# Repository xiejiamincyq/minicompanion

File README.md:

# Mini Companion · 微雪 2 英寸 BLE-A2

两台便携电子宠物样机，各用一块微雪 ESP32-S3 带屏核心和一块三键电源小板。侧面有实体开关，日常充电时硬件停机，电芯测温独立于固件。

**[打开最新 KiCad 工程](hardware/ble-economy/project/mini_companion_a2.kicad_pro)**　·　**[下载两台样机询价包（ZIP）](hardware/ble-economy/quote/Mini-Companion-A2-RFQ.zip?raw=true)**

- **编辑或看图**　解压询价包后，用 KiCad 10 打开 `project/mini_companion_a2.kicad_pro`。[原理图 PDF](hardware/ble-economy/verification/a2_schematic.pdf) · [顶面装配 PDF](hardware/ble-economy/verification/a2_top_assembly.pdf) · [外壳示意](hardware/ble-economy/mechanical/装配.md)
- **核价与代装**　[两台费用与预算上限](hardware/ble-economy/两台费用.md) · [线束及代装范围](hardware/ble-economy/sourcing/外部询价与免焊线束要求.md) · [逐台实物验收](hardware/ble-economy/整机验收.md)
- **开发与历史版本**　[蓝牙、USB 和按键接口](hardware/ble-economy/使用与软件接口.md) · [项目总入口](00-项目入口/先读我.md) · [上一版 BLE-A1](hardware/ble-review/README.md)

<details>
<summary>上游 Devotchi 项目说明（原版硬件、软件及文档）</summary>

# Devotchi

A Tamagotchi-style portable device that connects to AI coding agents (Claude Code, Cursor, etc.) via the Model Context Protocol (MCP). Your Devotchi shows what the agent is doing, handles approval requests via physical buttons, and its mood reflects the project's health.

Carry it in your pocket, clip it to your bag, or leave it on your desk — no need to stare at a terminal waiting for approval prompts. It vibrates, shows a nervous face, and waits for you to press a button.

## How it works

```
+------------------+          +---------------------+
|  User's PC       |          |  Server             |
|                  |  hooks   |                     |
|  Claude Code  ---|--------->|  Hook endpoints     |
|                  |          |  WebSocket router   |
|  MCP server   ---|--ws----->|  SQLite             |
|  (in client)     |          |                     |
+------------------+          +---------+-----------+
                                        |
                                        | WebSocket
                                        v
                              +---------------------+
                              |  Devotchi Device     |
                              |  (ESP32 + TFT LCD)   |
                              +---------------------+
```

1. **Claude Code hooks** automatically forward permission requests to the server via HTTP
2. The server sends them to your **Devotchi device** over WiFi (WebSocket)
3. You approve or reject directly on the device with physical buttons
4. The response goes back to Claude Code, which continues (or stops)
5. The **MCP server** lets the agent voluntarily send status updates, mood changes, and notifications

## Hardware

First prototype PCB, designed in KiCad and manufactured by JLCPCB.

- **MCU:** ESP32-S3-MINI-1 (dual-core 240MHz, WiFi + BLE, 4MB flash, 2MB PSRAM)
- **Display:** 2.0" IPS TFT LCD, 320x240, ST7789 driver, SPI interface
- **Input:** 3 tactile buttons (approve, reject, action) — any button press wakes from deep sleep
- **Power:** LiPo battery, USB-C charging (TP4056), DW01A protection, ME6211 3.3V LDO
- **Output:** Status LED, vibration motor

See [hardware/README.md](hardware/README.md) for full component details, pin assignments, and BOM.

## Project status

This is an active work-in-progress. The first prototype PCB has been designed and ordered. The software packages (server, client, web dashboard) are early prototypes being developed alongside the hardware.

## Repository structure

```
hardware/          KiCad schematics, PCB layout, BOM
firmware/          ESP32 firmware (C, ESP-IDF) — not yet started
packages/
  shared/          Protocol types and constants
  server/          WebSocket server + REST API + SQLite
  client/          CLI, MCP server, web dashboard
case/              3D-printable enclosure exploration
docs/              Architecture, protocol spec, datasheets
```

## Development

```bash
pnpm install
pnpm run build
pnpm run server    # Start server on :8080
pnpm run client    # Start client dashboard on :3456
```

## Documentation

- [Architecture](docs/architecture.md) — system overview, layers, data flow
- [Protocol](docs/protocol.md) — wire protocol specification
- [Hardware](hardware/README.md) — components, pin assignments, PCB design

## License

[MIT](LICENSE)

</details>

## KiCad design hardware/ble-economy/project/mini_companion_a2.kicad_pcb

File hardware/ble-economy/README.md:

# Mini Companion BLE-A2 · 两台样机

两块微雪 ESP32-S3-LCD-2 V2 各配一块定制三键电源板、一只带保护电池和一套树脂外壳。本版按两台样机设计。电气和装配资料供询价，实物制作、温度保护测试和总装验收待进行。

| 想看什么 | 文件 |
|---|---|
| 打开 KiCad 10 完整工程 | [工程文件](project/mini_companion_a2.kicad_pro) · [原理图](project/mini_companion_a2.kicad_sch) · [双层 PCB](project/mini_companion_a2.kicad_pcb) |
| 免安装看图 | [电路 PDF](verification/a2_schematic.pdf) · [顶面装配 PDF](verification/a2_top_assembly.pdf) · [壳体及安装](mechanical/装配.md) |
| 两台花多少钱 | [含线束、装配、运费的预算](两台费用.md) · [采购核验](sourcing/采购核验记录_20261119.md) |
| 让工厂单面贴片 | [嘉立创格式 BOM](sourcing/BOM_JLC_顶面.csv) · [顶面坐标](manufacturing/top-position-jlc.csv) · [光绘和钻孔](manufacturing/a2-gerber-drill.zip) · [贴装说明](manufacturing/README.md) |
| 让代装方免焊交付 | [询价范围及逐针接线](sourcing/外部询价与免焊线束要求.md) · [四款打印文件](mechanical/stl/) · [逐台验收表](整机验收.md) |
| 了解电路和软件接口 | [供电、互锁与温度计算](design/电气设计与验收.md) · [开关、按键、BLE 和 USB 烧录](使用与软件接口.md) |
| 复核设计文件 | [电路校核](verification/a2_electrical_checks.json) · [布线校核](verification/a2_pcb_receipt.json) · [机械校核](mechanical/geometry-check.json) |

USB-C 由运行短线和电脑数据线轮流使用。日常充电走单独的 5 V 圆口，圆口插入即关断电池给主机的供电。温感探头贴在电芯大面，由小板硬件禁充；代装方要为两台分别交付温度动作记录。[微雪核心](https://www.waveshare.net/shop/ESP32-S3-LCD-2.htm) · [芯片充电规格](https://www.ti.com/product/BQ25170)

用过的 KiCad 工具版本、用途和复查方式见[工具说明](tools/PCB工具说明.md)。本版可下载的硬件包及费用汇总从[项目总入口](../../00-项目入口/先读我.md)进入。

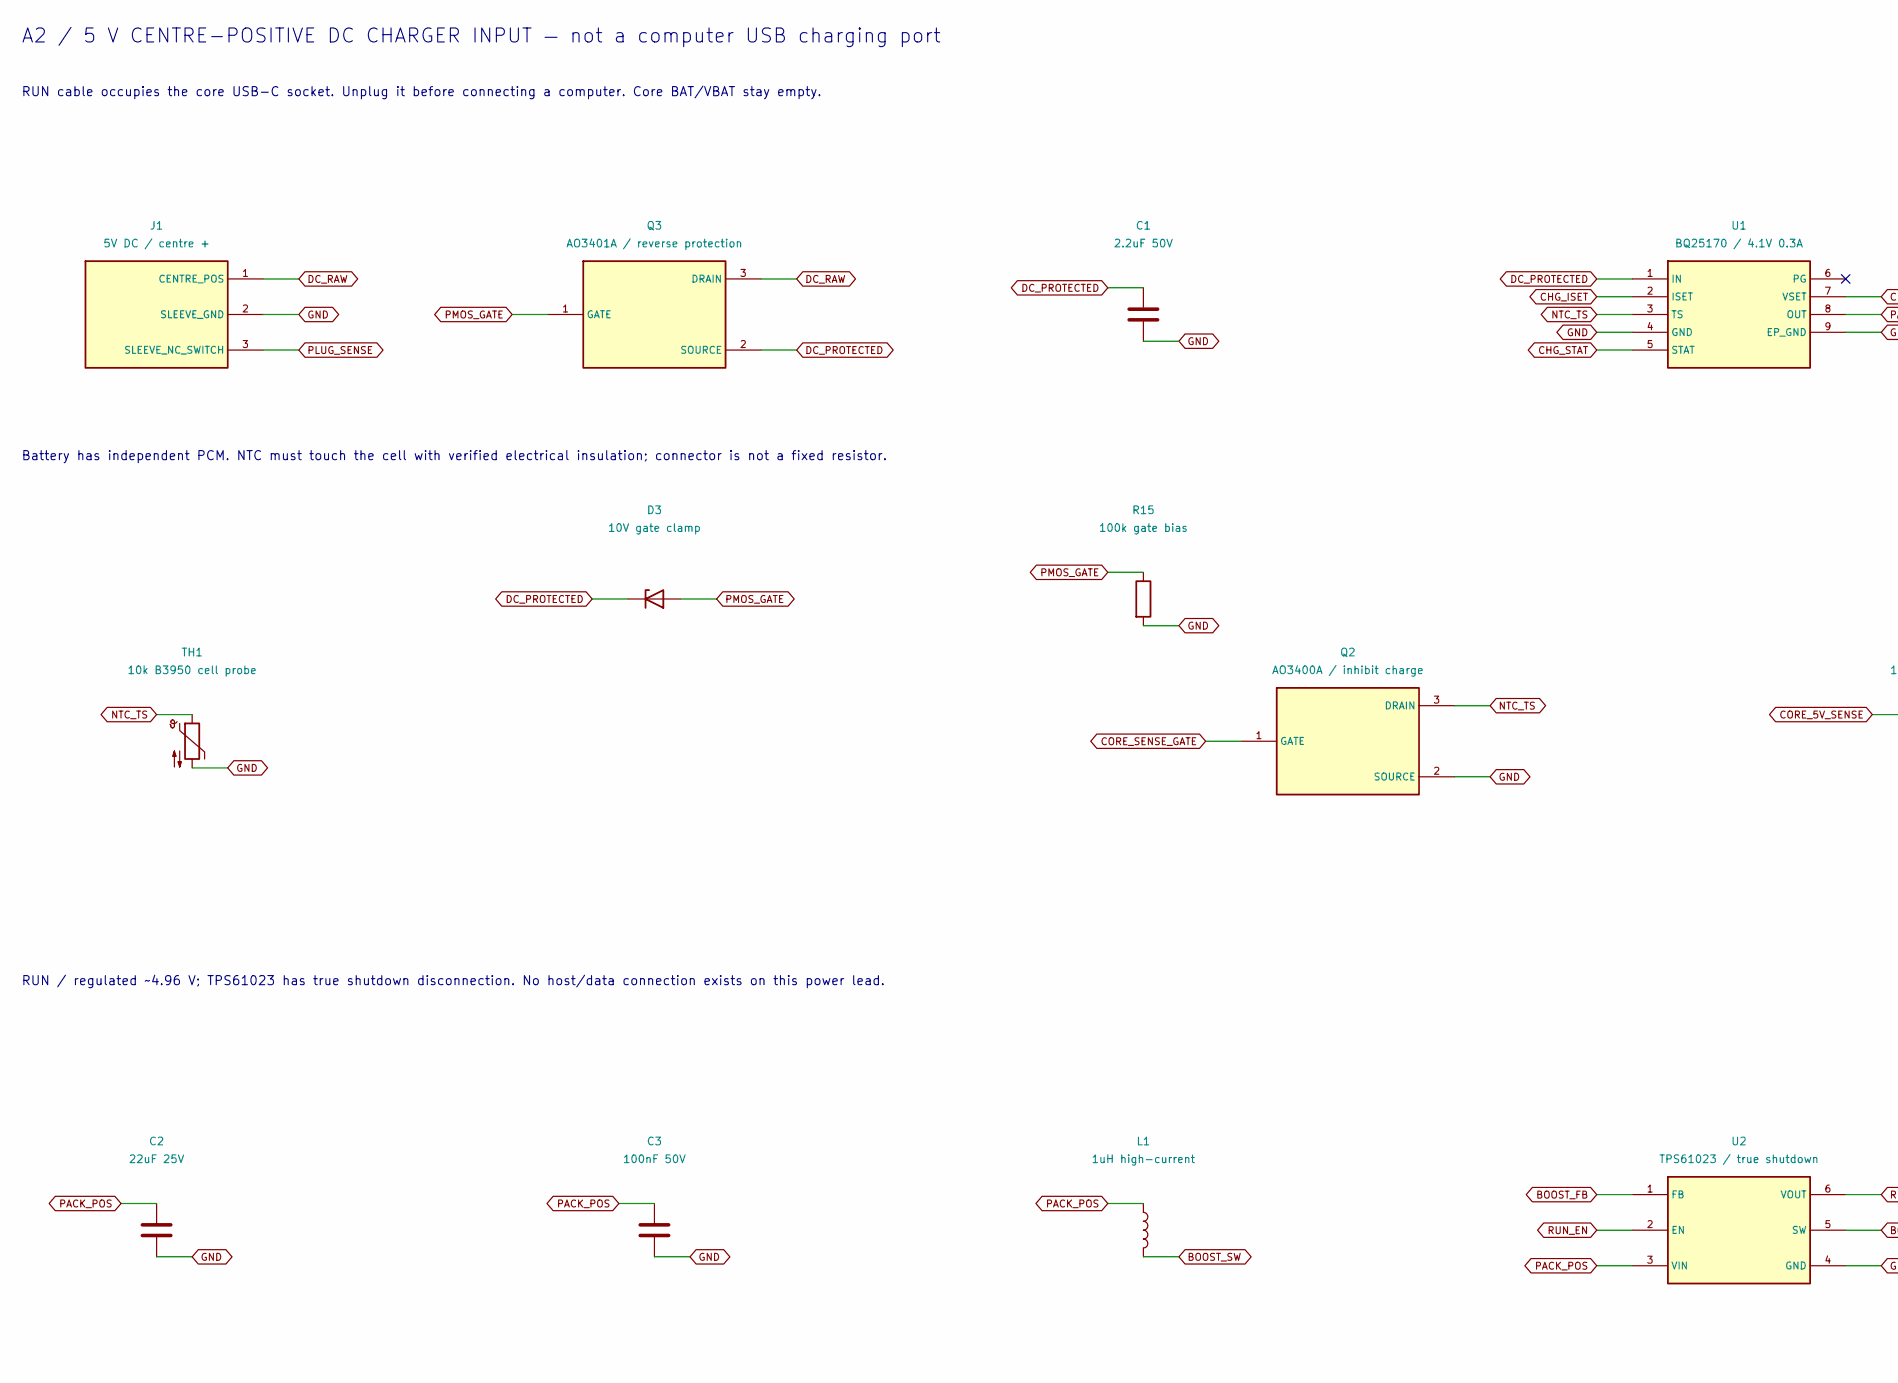
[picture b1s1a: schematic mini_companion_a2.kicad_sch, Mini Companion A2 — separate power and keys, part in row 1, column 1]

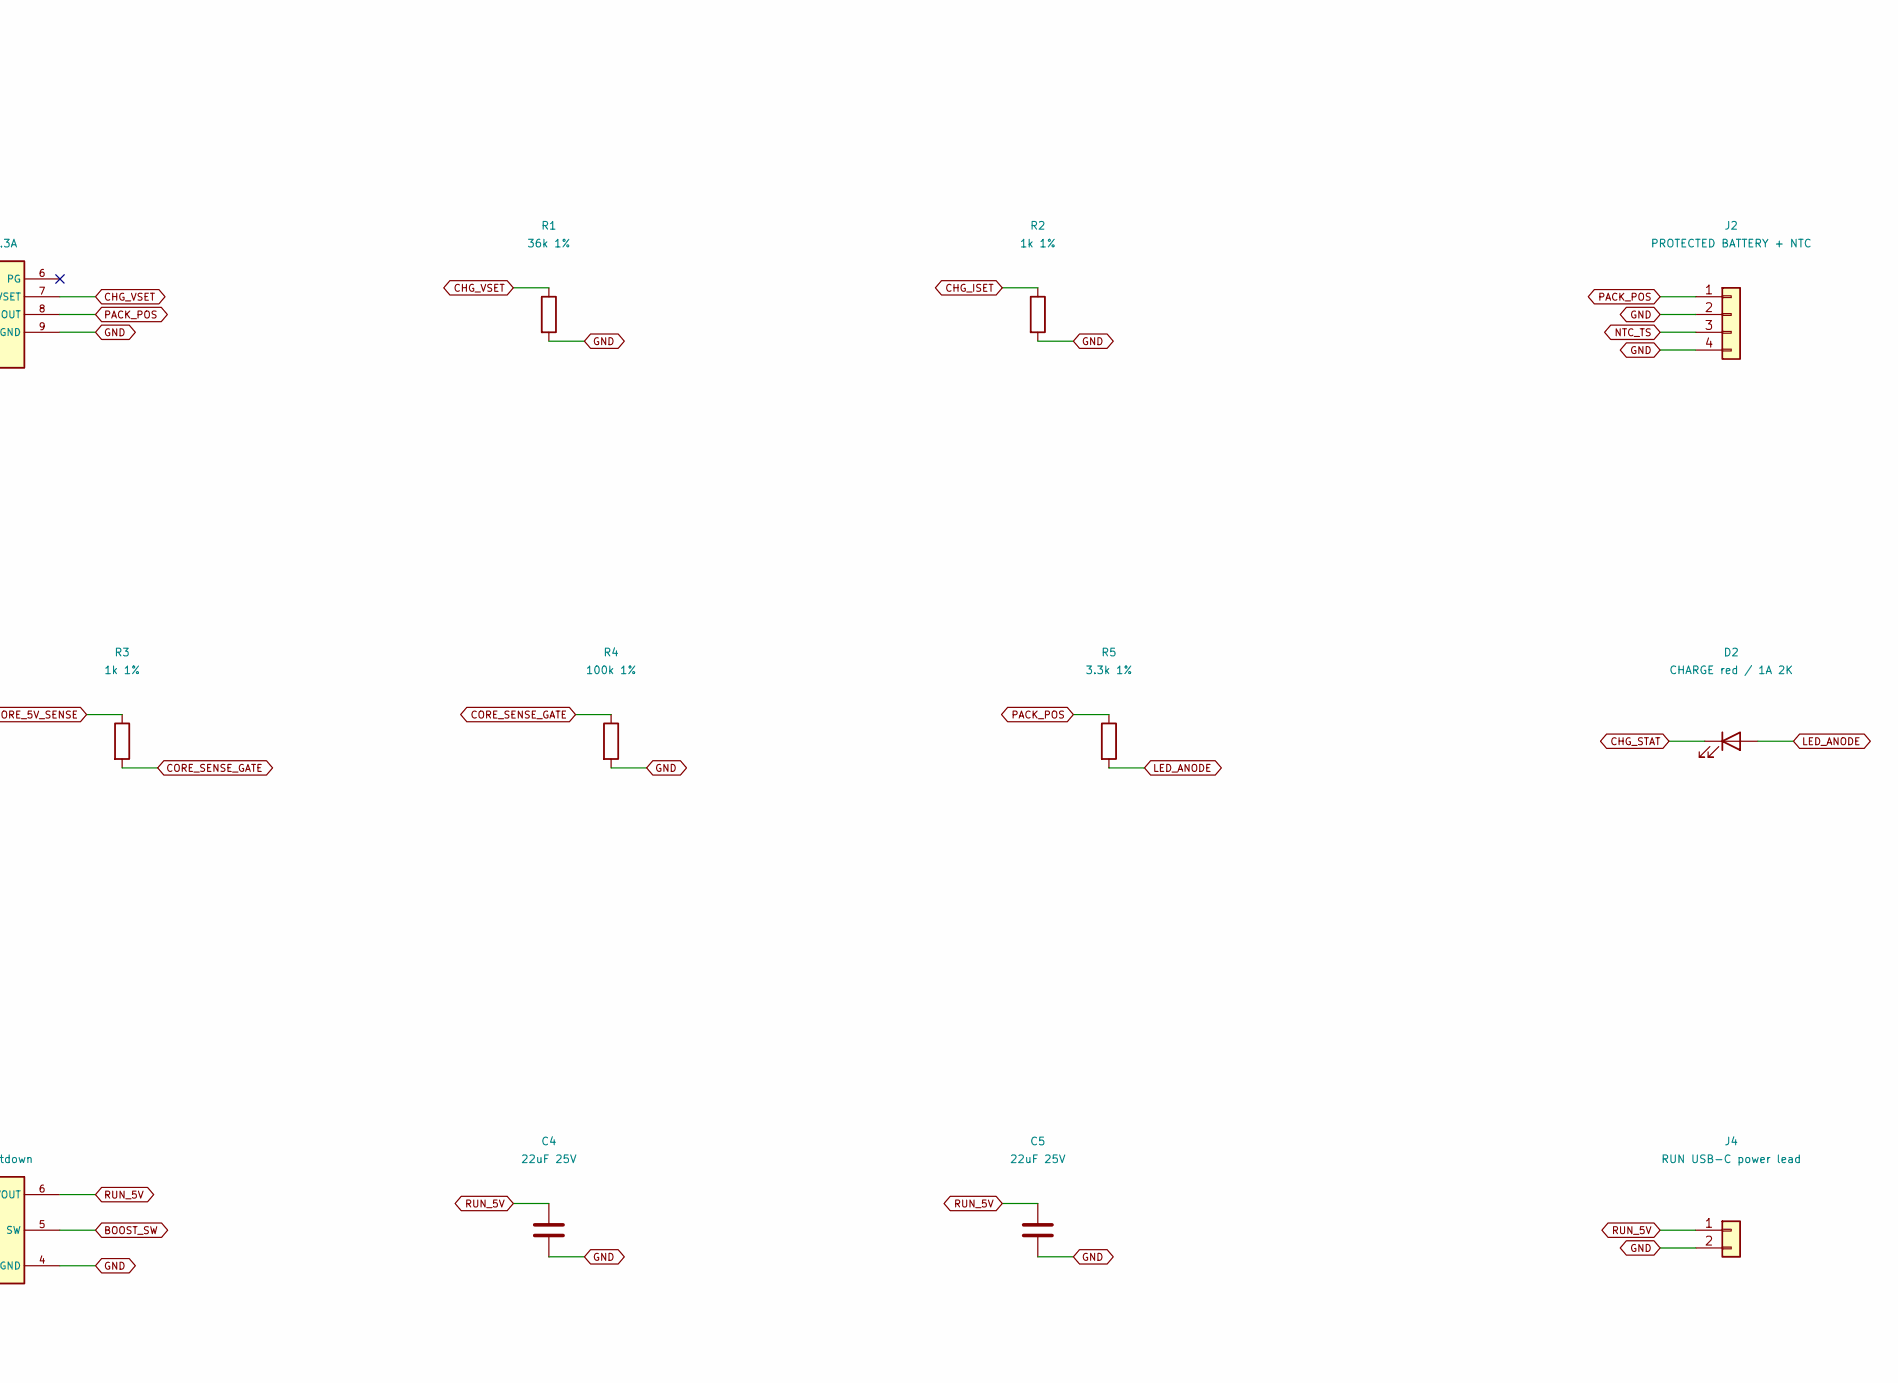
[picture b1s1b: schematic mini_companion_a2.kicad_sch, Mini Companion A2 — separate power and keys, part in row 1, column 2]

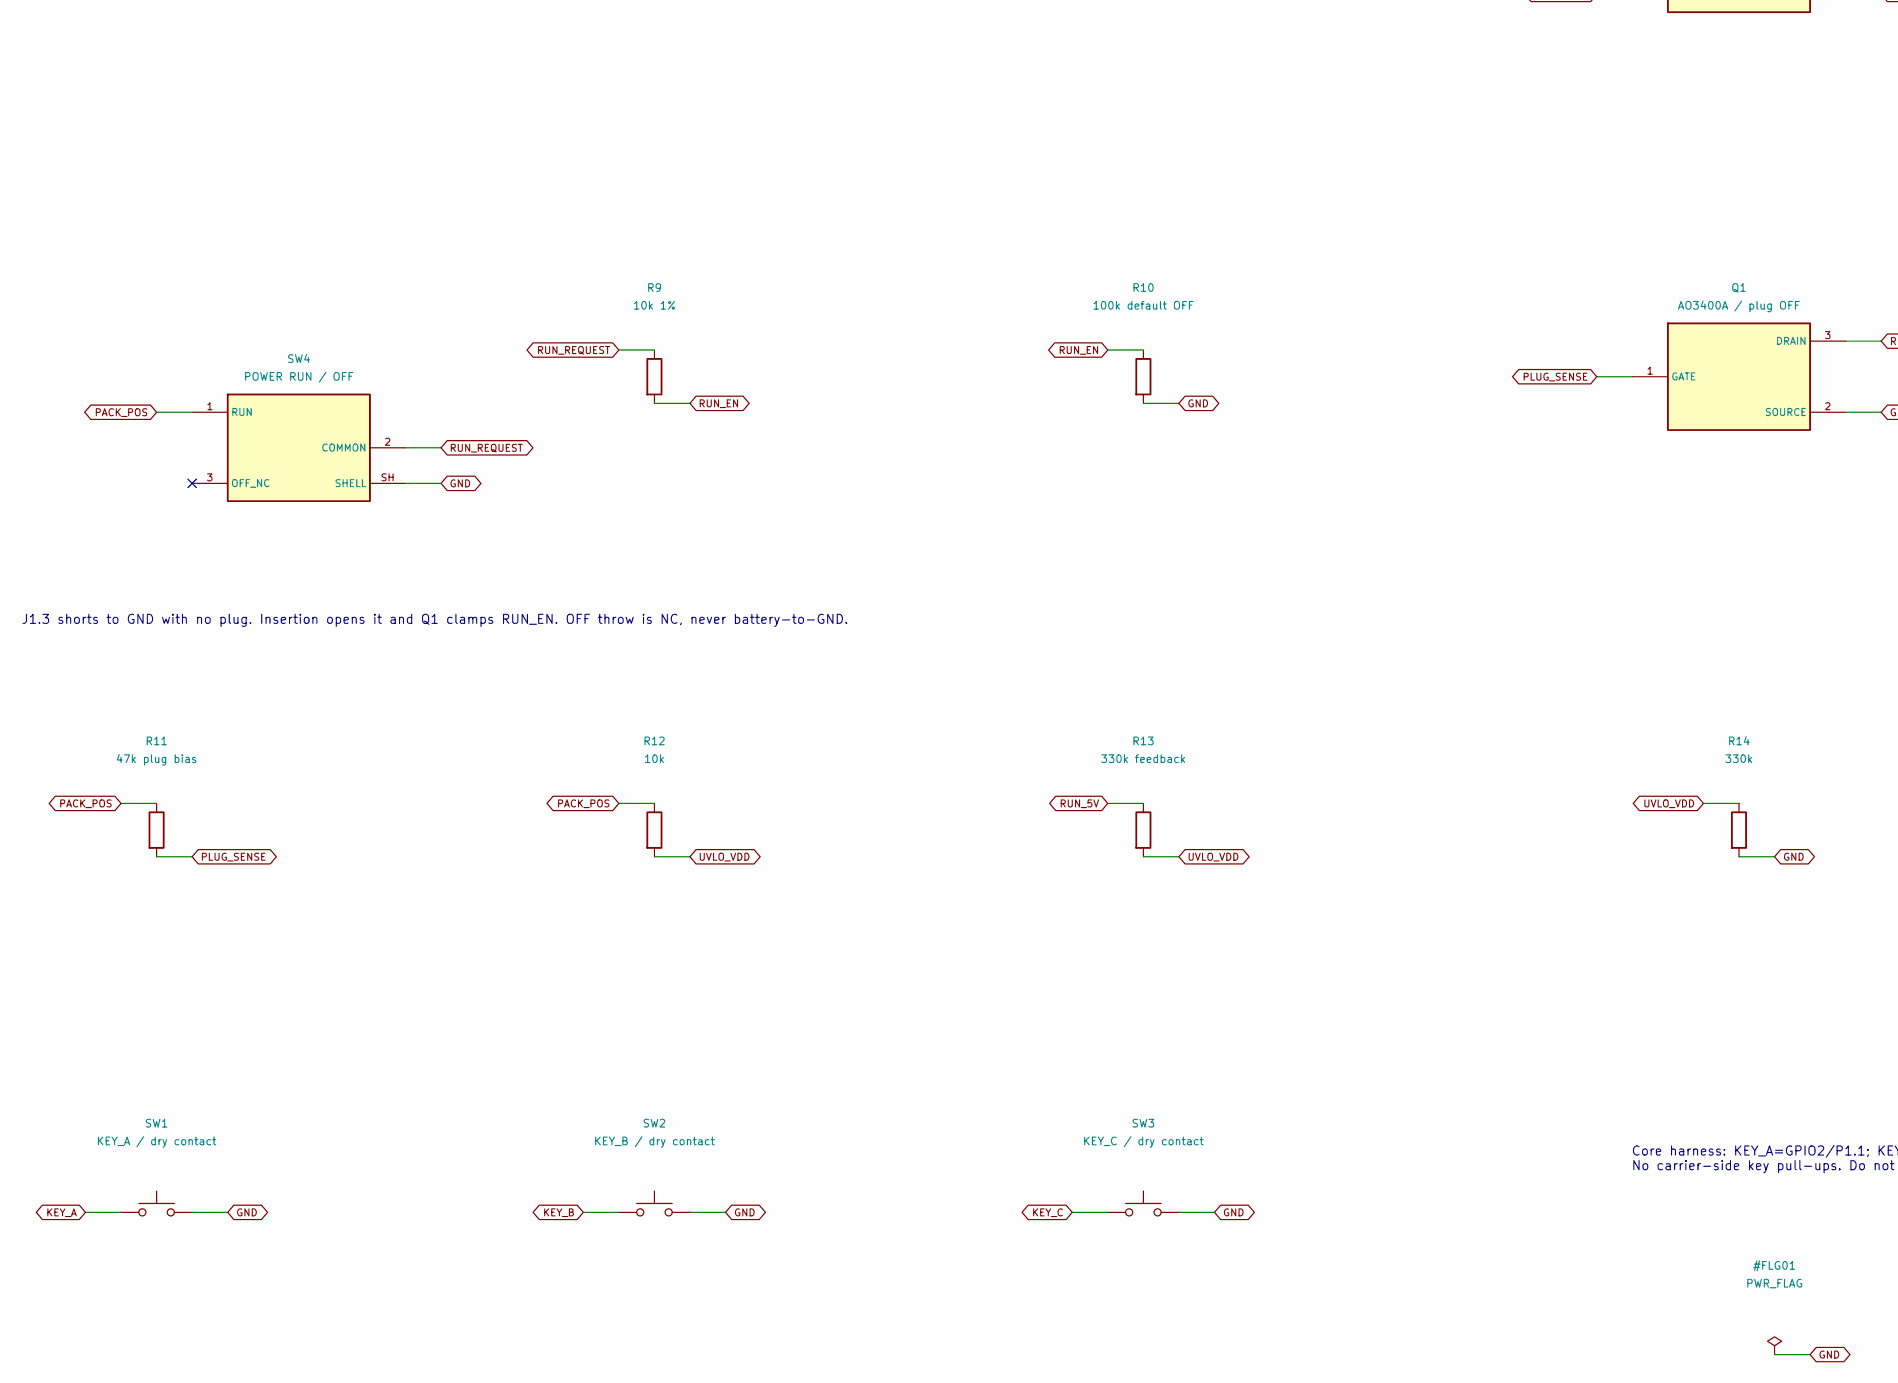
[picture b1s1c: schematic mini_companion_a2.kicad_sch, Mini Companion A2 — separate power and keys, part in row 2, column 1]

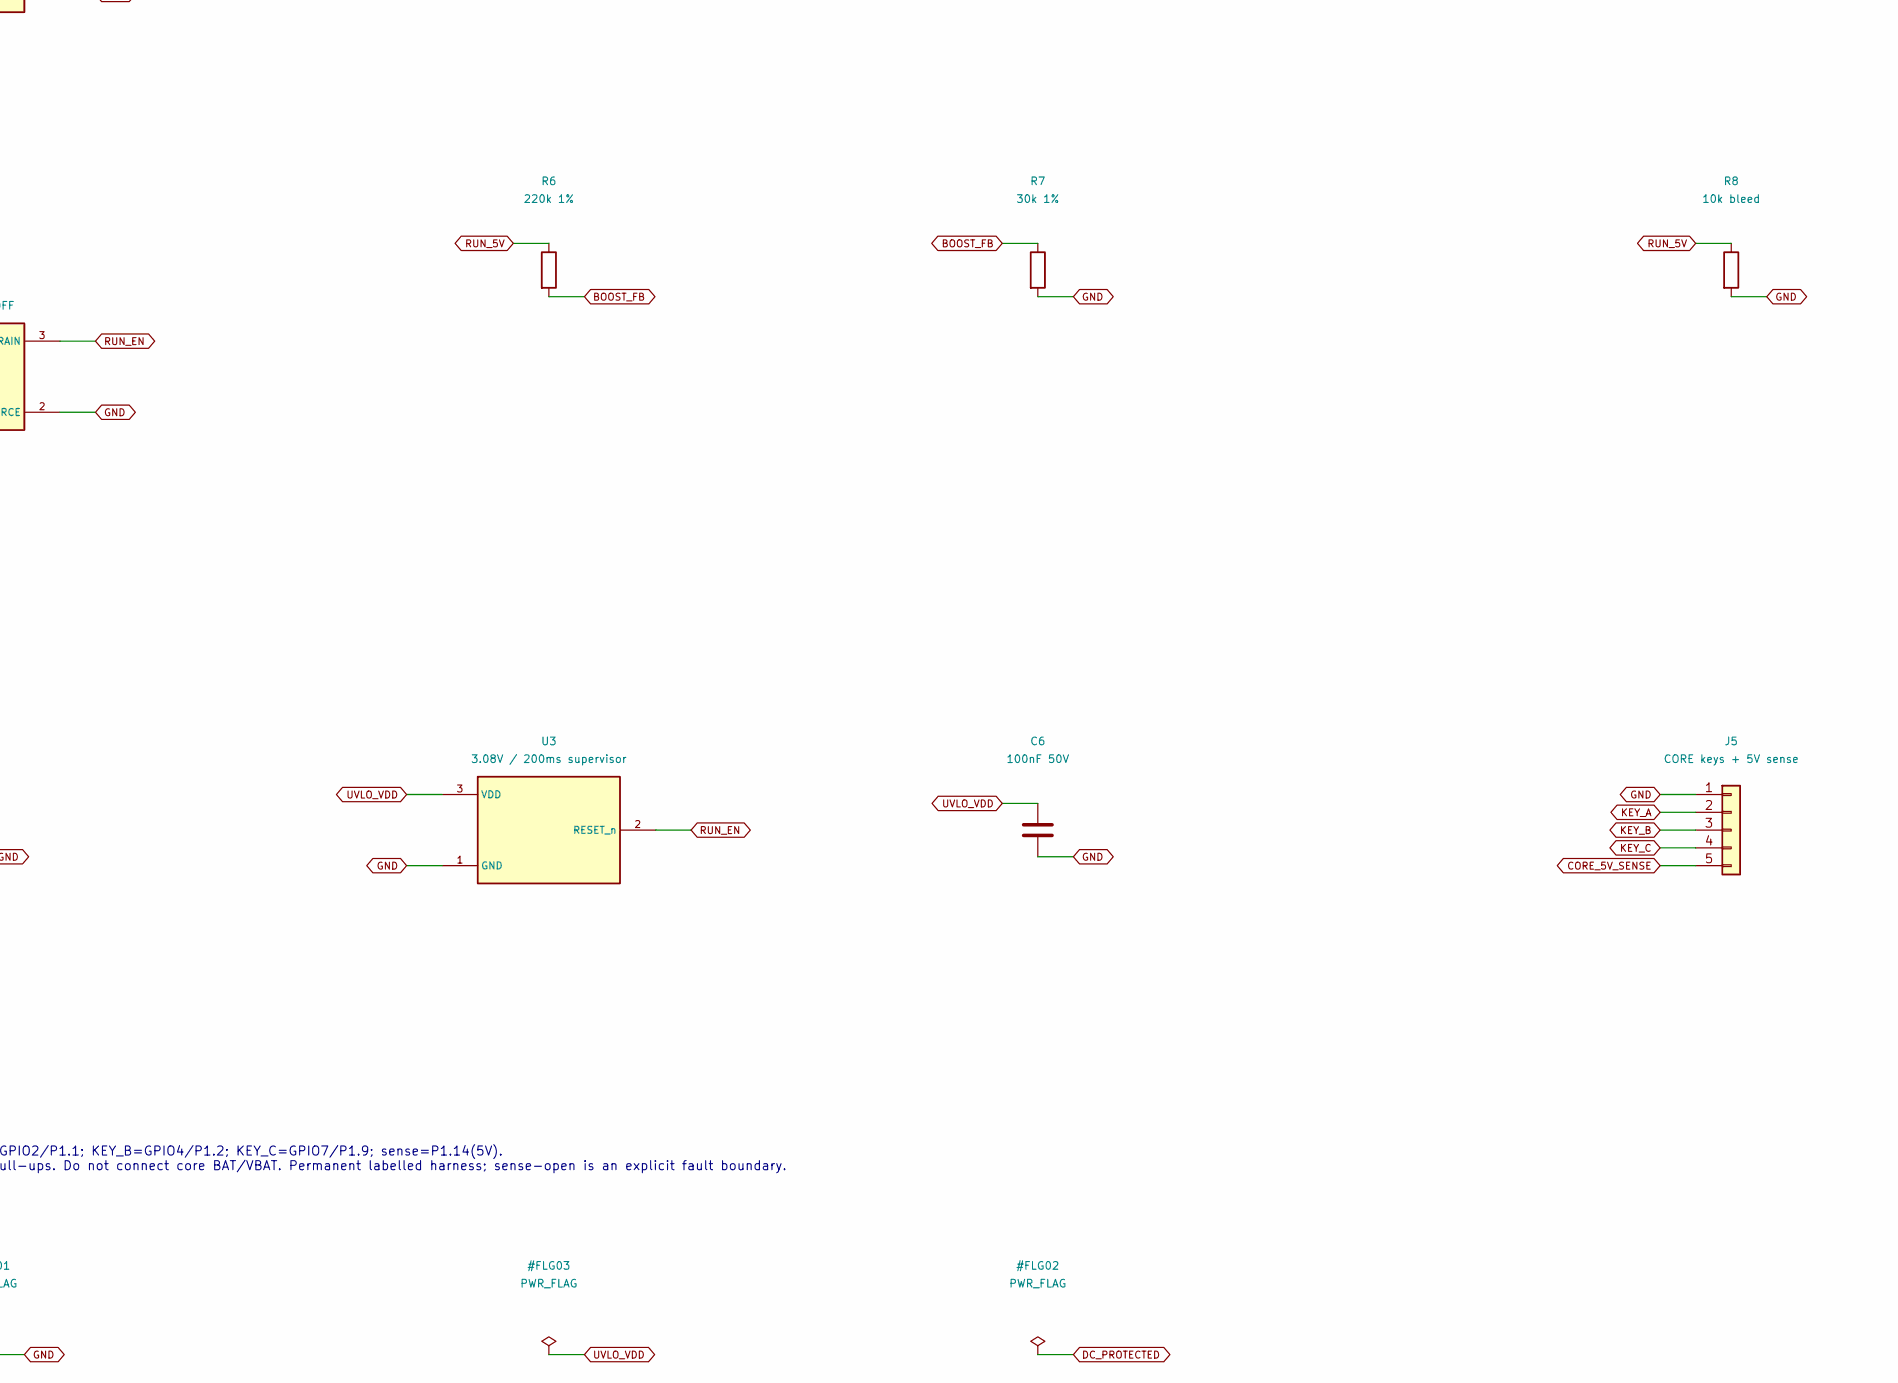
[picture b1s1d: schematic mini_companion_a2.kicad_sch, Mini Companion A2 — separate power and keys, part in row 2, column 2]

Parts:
C1: 2.2uF 50V; C_0805_2012Metric; MPN CL21B225KBYNNNE; LCSC C2762602
C2, C4, C5: 22uF 25V; C_0805_2012Metric; MPN CL21A226MAQNNNE; LCSC C45783
C3, C6: 100nF 50V; C_0603_1608Metric; MPN CC0603KRX7R9BB104; LCSC C14663
D2: CHARGE red / 1A 2K; KT-0603R; MPN KT-0603R; LCSC C2286
D3: 10V gate clamp; D_SOD-123; MPN BZT52C10; LCSC C2103
J1: 5V DC / centre +; DC-050-2.0-BD; MPN DC-050-2.0-BD; LCSC C51927418
J2: PROTECTED BATTERY + NTC; JST_PH_B4B-PH-SM4-TB_1x04-1MP_P2.00mm_Vertical; MPN B4B-PH-SM4-TB(LF)(SN); LCSC C160354
J4: RUN USB-C power lead; JST_PH_B2B-PH-SM4-TB_1x02-1MP_P2.00mm_Vertical; MPN B2B-PH-SM4-TB(LF)(SN); LCSC C160352
J5: CORE keys + 5V sense; JST_PH_B5B-PH-SM4-TB_1x05-1MP_P2.00mm_Vertical; MPN B5B-PH-SM4-TB(LF)(SN); LCSC C265085
L1: 1uH high-current; FTC404030S1R0MGCA; MPN FTC404030S1R0MGCA; LCSC C39676079
Q1: AO3400A / plug OFF; SOT-23; MPN AO3400A; LCSC C20917
Q2: AO3400A / inhibit charge; SOT-23; MPN AO3400A; LCSC C20917
Q3: AO3401A / reverse protection; SOT-23; MPN AO3401A; LCSC C15127
R1: 36k 1%; R_0603_1608Metric; MPN 0603WAF3602T5E; LCSC C23147
R2, R3: 1k 1%; R_0603_1608Metric; MPN 0603WAF1001T5E; LCSC C21190
R4: 100k 1%; R_0603_1608Metric; MPN 0603WAF1003T5E; LCSC C25803
R5: 3.3k 1%; R_0603_1608Metric; MPN 0603WAF3301T5E; LCSC C22978
R6: 220k 1%; R_0603_1608Metric; MPN 0603WAF2203T5E; LCSC C22961
R7: 30k 1%; R_0603_1608Metric; MPN 0603WAF3002T5E; LCSC C22984
R8: 10k bleed; R_0603_1608Metric; MPN 0603WAF1002T5E; LCSC C25804
R9: 10k 1%; R_0603_1608Metric; MPN 0603WAF1002T5E; LCSC C25804
R10: 100k default OFF; R_0603_1608Metric; MPN 0603WAF1003T5E; LCSC C25803
R11: 47k plug bias; R_0603_1608Metric; MPN 0603WAF4702T5E; LCSC C25819
R12: 10k; R_0603_1608Metric; MPN 0603WAF1002T5E; LCSC C25804
R13: 330k feedback; R_0603_1608Metric; MPN 0603WAF3303T5E; LCSC C23137
R14: 330k; R_0603_1608Metric; MPN 0603WAF3303T5E; LCSC C23137
R15: 100k gate bias; R_0603_1608Metric; MPN 0603WAF1003T5E; LCSC C25803
SW1: KEY_A / dry contact; SW_Push_1P1T_XKB_TS-1187A; MPN TS-1187A-B-A-B; LCSC C318884
SW2: KEY_B / dry contact; SW_Push_1P1T_XKB_TS-1187A; MPN TS-1187A-B-A-B; LCSC C318884
SW3: KEY_C / dry contact; SW_Push_1P1T_XKB_TS-1187A; MPN TS-1187A-B-A-B; LCSC C318884
SW4: POWER RUN / OFF; SW_SPDT_Shouhan_MSK12C02; MPN MSK12C02; LCSC C431540
TH1: 10k B3950 cell probe; MPN HNTC-103F3950FB-100B; LCSC C52204609
U1: BQ25170 / 4.1V 0.3A; Texas_DSG0008A_WSON-8-1EP_2x2mm_P0.5mm_EP0.9x1.6mm; MPN BQ25170DSGR; LCSC C5208201
U2: TPS61023 / true shutdown; SOT-563; MPN TPS61023DRLR; LCSC C919459
U3: 3.08V / 200ms supervisor; SOT-23; MPN TLV803EA30DBZR; LCSC C5218924

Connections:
BOOST_FB: R6.2, R7.1, U2.1 (FB)
BOOST_SW: L1.2, U2.5 (SW)
CHG_ISET: R2.1, U1.2 (ISET)
CHG_STAT: D2.2 (K), U1.5 (STAT)
CHG_VSET: R1.1, U1.7 (VSET)
CORE_5V_SENSE: J5.5, R3.1
CORE_SENSE_GATE: Q2.1 (GATE), R3.2, R4.1
DC_PROTECTED: C1.1, D3.1 (K), Q3.2 (SOURCE), U1.1 (IN)
DC_RAW: J1.1 (CENTRE_POS), Q3.3 (DRAIN)
GND: C1.2, C2.2, C3.2, C4.2, C5.2, C6.2, J1.2 (SLEEVE_GND), J2.2, J2.4, J4.2, J5.1, Q1.2 (SOURCE), Q2.2 (SOURCE), R1.2, R2.2, R4.2, R7.2, R8.2, R10.2, R14.2, R15.2, SW1.2, SW2.2, SW3.2, SW4.SH (SHELL), TH1.2, U1.4 (GND), U1.9 (EP_GND), U2.4 (GND), U3.1 (GND)
KEY_A: J5.2, SW1.1
KEY_B: J5.3, SW2.1
KEY_C: J5.4, SW3.1
LED_ANODE: D2.1 (A), R5.2
NTC_TS: J2.3, Q2.3 (DRAIN), TH1.1, U1.3 (TS)
PACK_POS: C2.1, C3.1, J2.1, L1.1, R5.1, R11.1, R12.1, SW4.1 (RUN), U1.8 (OUT), U2.3 (VIN)
PLUG_SENSE: J1.3 (SLEEVE_NC_SWITCH), Q1.1 (GATE), R11.2
PMOS_GATE: D3.2 (A), Q3.1 (GATE), R15.1
RUN_5V: C4.1, C5.1, J4.1, R6.1, R8.1, R13.1, U2.6 (VOUT)
RUN_EN: Q1.3 (DRAIN), R9.2, R10.1, U2.2 (EN), U3.2 (RESET_n)
RUN_REQUEST: R9.1, SW4.2 (COMMON)
UVLO_VDD: C6.1, R12.2, R13.2, R14.1, U3.3 (VDD)

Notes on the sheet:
A2 / 5 V CENTRE-POSITIVE DC CHARGER INPUT — not a computer USB charging port
RUN cable occupies the core USB-C socket. Unplug it before connecting a computer. Core BAT/VBAT stay empty.
Battery has independent PCM. NTC must touch the cell with verified electrical insulation; connector is not a fixed resistor.
RUN / regulated ~4.96 V; TPS61023 has true shutdown disconnection. No host/data connection exists on this power lead.
J1.3 shorts to GND with no plug. Insertion opens it and Q1 clamps RUN_EN. OFF throw is NC, never battery-to-GND.
Core harness: KEY_A=GPIO2/P1.1; KEY_B=GPIO4/P1.2; KEY_C=GPIO7/P1.9; sense=P1.14(5V). No carrier-side key pull-ups. Do not connect core BAT/VBAT. Permanent labelled harness; sense-open is an explicit fault boundary.

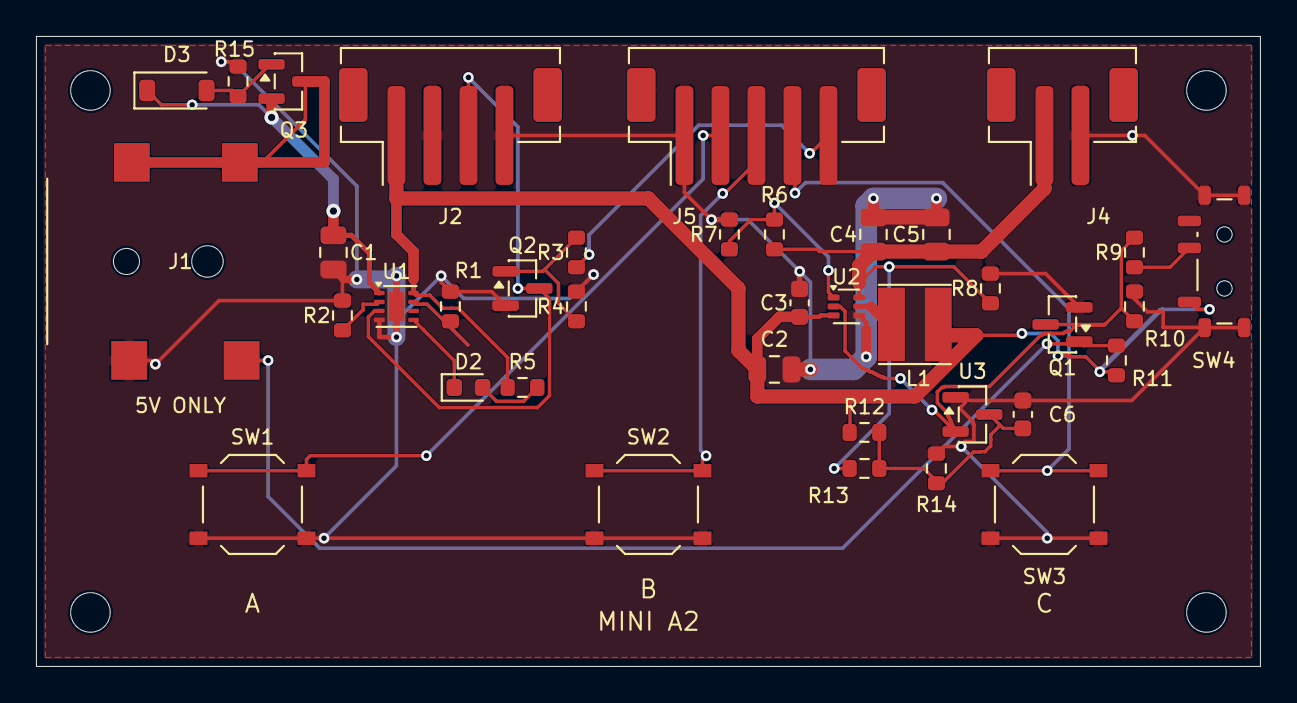
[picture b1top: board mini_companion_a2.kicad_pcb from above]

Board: 2 copper layers, 68.0 x 35.0 mm, 42 parts (0 on the bottom side), 22 nets.

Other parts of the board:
H1, H2, H3, H4: M2; MountingHole_2.2mm_M2

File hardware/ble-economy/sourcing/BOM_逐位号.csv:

Ref,Value,MPN,LCSC,Manufacturer,Footprint,AssemblyDomain
C1,2.2uF 50V,CL21B225KBYNNNE,C2762602,Samsung Electro-Mechanics,Capacitor_SMD:C_0805_2012Metric,main
C2,22uF 25V,CL21A226MAQNNNE,C45783,Samsung Electro-Mechanics,Capacitor_SMD:C_0805_2012Metric,main
C3,100nF 50V,CC0603KRX7R9BB104,C14663,YAGEO,Capacitor_SMD:C_0603_1608Metric,main
C4,22uF 25V,CL21A226MAQNNNE,C45783,Samsung Electro-Mechanics,Capacitor_SMD:C_0805_2012Metric,main
C5,22uF 25V,CL21A226MAQNNNE,C45783,Samsung Electro-Mechanics,Capacitor_SMD:C_0805_2012Metric,main
C6,100nF 50V,CC0603KRX7R9BB104,C14663,YAGEO,Capacitor_SMD:C_0603_1608Metric,main
D2,CHARGE red / 1A 2K,KT-0603R,C2286,KENTO,A2_Candidate:KT-0603R,main
D3,10V gate clamp,BZT52C10,C2103,Jiangsu Changjing Electronics,Diode_SMD:D_SOD-123,main
J1,5V DC / centre +,DC-050-2.0-BD,C51927418,CAX,A2_Candidate:DC-050-2.0-BD,main
J2,PROTECTED BATTERY + NTC,B4B-PH-SM4-TB(LF)(SN),C160354,JST,Connector_JST:JST_PH_B4B-PH-SM4-TB_1x04-1MP_P2.00mm_Vertical,main
J4,RUN USB-C power lead,B2B-PH-SM4-TB(LF)(SN),C160352,JST,Connector_JST:JST_PH_B2B-PH-SM4-TB_1x02-1MP_P2.00mm_Vertical,main
J5,CORE keys + 5V sense,B5B-PH-SM4-TB(LF)(SN),C265085,JST,Connector_JST:JST_PH_B5B-PH-SM4-TB_1x05-1MP_P2.00mm_Vertical,main
L1,1uH high-current,FTC404030S1R0MGCA,C39676079,cjiang (Changjiang),A2_Candidate:FTC404030S1R0MGCA,main
Q1,AO3400A / plug OFF,AO3400A,C20917,Alpha and Omega Semiconductor,Package_TO_SOT_SMD:SOT-23,main
Q2,AO3400A / inhibit charge,AO3400A,C20917,Alpha and Omega Semiconductor,Package_TO_SOT_SMD:SOT-23,main
Q3,AO3401A / reverse protection,AO3401A,C15127,Alpha and Omega Semiconductor,Package_TO_SOT_SMD:SOT-23,main
R1,36k 1%,0603WAF3602T5E,C23147,UNI-ROYAL,Resistor_SMD:R_0603_1608Metric,main
R2,1k 1%,0603WAF1001T5E,C21190,UNI-ROYAL,Resistor_SMD:R_0603_1608Metric,main
R3,1k 1%,0603WAF1001T5E,C21190,UNI-ROYAL,Resistor_SMD:R_0603_1608Metric,main
R4,100k 1%,0603WAF1003T5E,C25803,UNI-ROYAL,Resistor_SMD:R_0603_1608Metric,main
R5,3.3k 1%,0603WAF3301T5E,C22978,UNI-ROYAL,Resistor_SMD:R_0603_1608Metric,main
R6,220k 1%,0603WAF2203T5E,C22961,UNI-ROYAL,Resistor_SMD:R_0603_1608Metric,main
R7,30k 1%,0603WAF3002T5E,C22984,UNI-ROYAL,Resistor_SMD:R_0603_1608Metric,main
R8,10k bleed,0603WAF1002T5E,C25804,UNI-ROYAL,Resistor_SMD:R_0603_1608Metric,main
R9,10k 1%,0603WAF1002T5E,C25804,UNI-ROYAL,Resistor_SMD:R_0603_1608Metric,main
R10,100k default OFF,0603WAF1003T5E,C25803,UNI-ROYAL,Resistor_SMD:R_0603_1608Metric,main
R11,47k plug bias,0603WAF4702T5E,C25819,UNI-ROYAL,Resistor_SMD:R_0603_1608Metric,main
R12,10k,0603WAF1002T5E,C25804,UNI-ROYAL,Resistor_SMD:R_0603_1608Metric,main
R13,330k feedback,0603WAF3303T5E,C23137,UNI-ROYAL,Resistor_SMD:R_0603_1608Metric,main
R14,330k,0603WAF3303T5E,C23137,UNI-ROYAL,Resistor_SMD:R_0603_1608Metric,main
R15,100k gate bias,0603WAF1003T5E,C25803,UNI-ROYAL,Resistor_SMD:R_0603_1608Metric,main
SW1,KEY_A / dry contact,TS-1187A-B-A-B,C318884,XKB,Button_Switch_SMD:SW_Push_1P1T_XKB_TS-1187A,main
SW2,KEY_B / dry contact,TS-1187A-B-A-B,C318884,XKB,Button_Switch_SMD:SW_Push_1P1T_XKB_TS-1187A,main
SW3,KEY_C / dry contact,TS-1187A-B-A-B,C318884,XKB,Button_Switch_SMD:SW_Push_1P1T_XKB_TS-1187A,main
SW4,POWER RUN / OFF,MSK12C02,C431540,SHOU HAN,Button_Switch_SMD:SW_SPDT_Shouhan_MSK12C02,main
TH1,10k B3950 cell probe,HNTC-103F3950FB-100B,C52204609,HNTC,,battery_probe
U1,BQ25170 / 4.1V 0.3A,BQ25170DSGR,C5208201,Texas Instruments,Package_SON:Texas_DSG0008A_WSON-8-1EP_2x2mm_P0.5mm_EP0.9x1.6mm,main
U2,TPS61023 / true shutdown,TPS61023DRLR,C919459,Texas Instruments,Package_TO_SOT_SMD:SOT-563,main
U3,3.08V / 200ms supervisor,TLV803EA30DBZR,C5218924,Texas Instruments,Package_TO_SOT_SMD:SOT-23,main

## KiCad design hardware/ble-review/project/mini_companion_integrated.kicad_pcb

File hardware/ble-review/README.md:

# Mini Companion BLE-A1｜两台样机硬件

**当前交付状态：可评审、可询价。** KiCad 10.0.6 保存态 ERC、全严重度严格 DRC、未连接、原理图与 PCB 一致性问题均为零。两台实物及含税到手报价待取得。

| 你要做什么 | 打开这里 |
|---|---|
| 查看图纸 | [完整原理图 PDF](quote/Schematic.pdf) · [KiCad 工程](project/mini_companion_integrated.kicad_pro) |
| 查看主板正反面 | [正面 PDF](verification/pcb_front.pdf) · [背面 PDF](verification/pcb_back.pdf) |
| 找供应商报价 | [两台完整询价 ZIP](quote/Mini-Companion-RFQ.zip) · [范围与三种加工路线](sourcing/供应商询价草稿_未发送.md) |
| 评估成本和缺料 | [内部预算与物料说明](sourcing/README.md) · [缺料备选](sourcing/缺料替代核对_20261119.md) |
| 后续写固件 | [GPIO、供电与软件接口](design/硬件与固件接口.md) · [普通 USB 线烧录与恢复](design/USB服务模式设计依据.md) |
| 看外壳或安排代装 | [后盖维护孔、打印件与装配](mechanical/README.md) · [两线 POWER、探头与线束](sourcing/线束与探头代装要求.md) |
| 核对版本 | [最终文件指纹](quote/manifest.json) · [ERC](quote/ERC.json) · [DRC](quote/DRC.json) · [基线及工具核验](verification/README.md) |

从 11 月 13 日的 BLE-A0 迁入。BLE-A1 保留 ESP32-S3、彩屏、三键、受保护电池和双机/手机 BLE。正常插线充电时停机。需要开发时，用有电的电池和背面维护开关切换为 USB 烧录；首次 ROM 恢复的设计期步骤见上表。为降低首次费用与结构工作量，本版省去声音器件。

主板每台 94 个需要采购并装配的器件，合并为 48 个物料行。目标为两台 400–600 元，整个项目支出上限 1000 元。电池、电芯温度探头、线束、屏幕和外壳加工均纳入询价。正式金额需供应商确认。下一步实物验收优先验证充电温升、烧录恢复、低电压/无线发射时的主轨、闭壳 BLE 与实测续航。

USB 只按 Full-Speed 开发口评审。两种插入方向下，D+/D− 的板上路径长度差分别约 24.8 mm、19.6 mm。需用普通数据线做双向枚举、故障恢复、整镜像烧录和回读校验。[走线度量](verification/usb_route_metrics.json)。

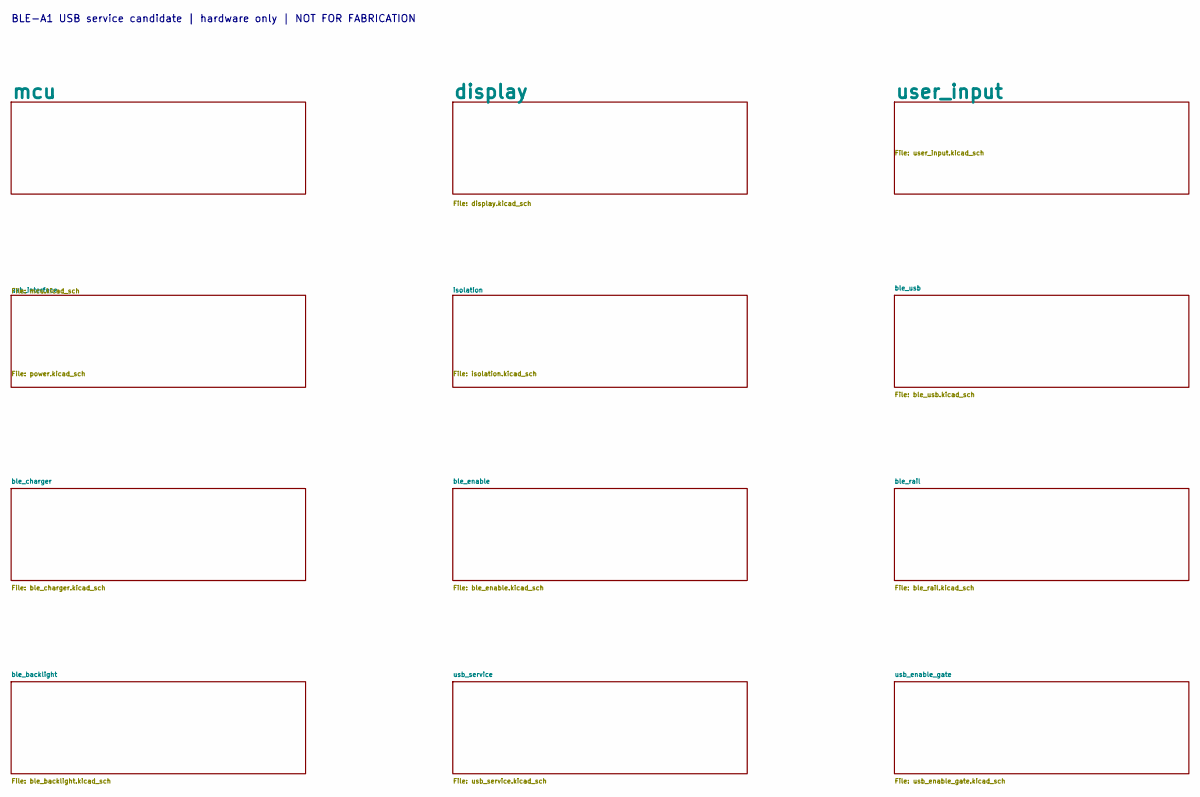
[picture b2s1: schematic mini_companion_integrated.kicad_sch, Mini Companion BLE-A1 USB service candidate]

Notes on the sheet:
BLE-A1 USB service candidate | hardware only | NOT FOR FABRICATION

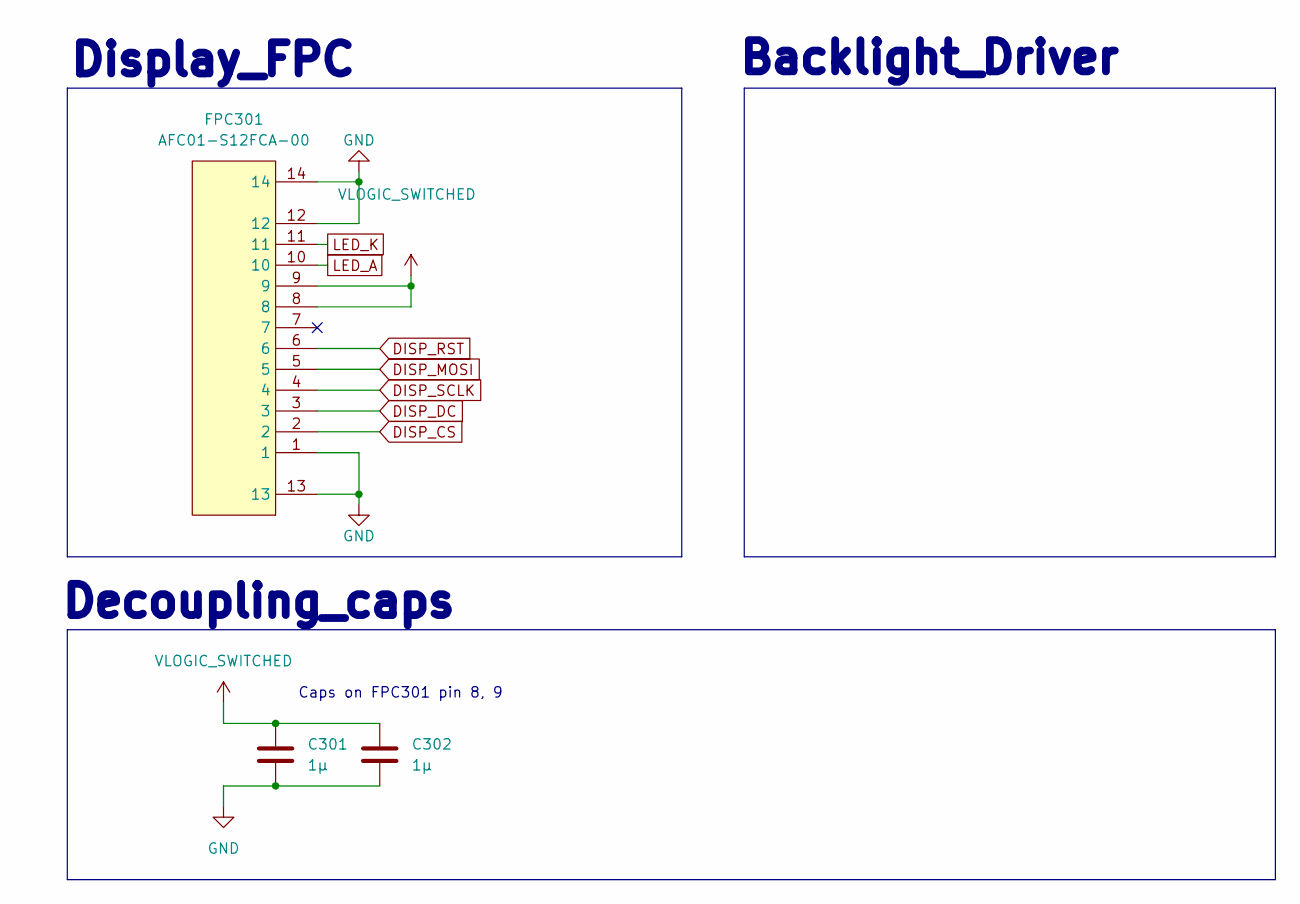
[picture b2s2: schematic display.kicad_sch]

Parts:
C301, C302: 1µ; C_0603_1608Metric_Pad1.08x0.95mm_HandSolder; LCSC Part C15849
FPC301: AFC01-S12FCA-00; FPC-SMD_AFC01-S12FCA-00; LCSC Part C262661

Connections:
DISP_CS: FPC301.2; also elsewhere on the board
DISP_DC: FPC301.3; also elsewhere on the board
DISP_MOSI: FPC301.5; also elsewhere on the board
DISP_RST: FPC301.6; also elsewhere on the board
DISP_SCLK: FPC301.4; also elsewhere on the board
GND: C301.2, C302.2, FPC301.1, FPC301.12, FPC301.13, FPC301.14; also elsewhere on the board
LED_A: FPC301.10; also elsewhere on the board
LED_K: FPC301.11; also elsewhere on the board
VLOGIC_SWITCHED: C301.1, C302.1, FPC301.8, FPC301.9; also elsewhere on the board

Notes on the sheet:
Decoupling_caps
Caps on FPC301 pin 8, 9
Display_FPC
Backlight_Driver

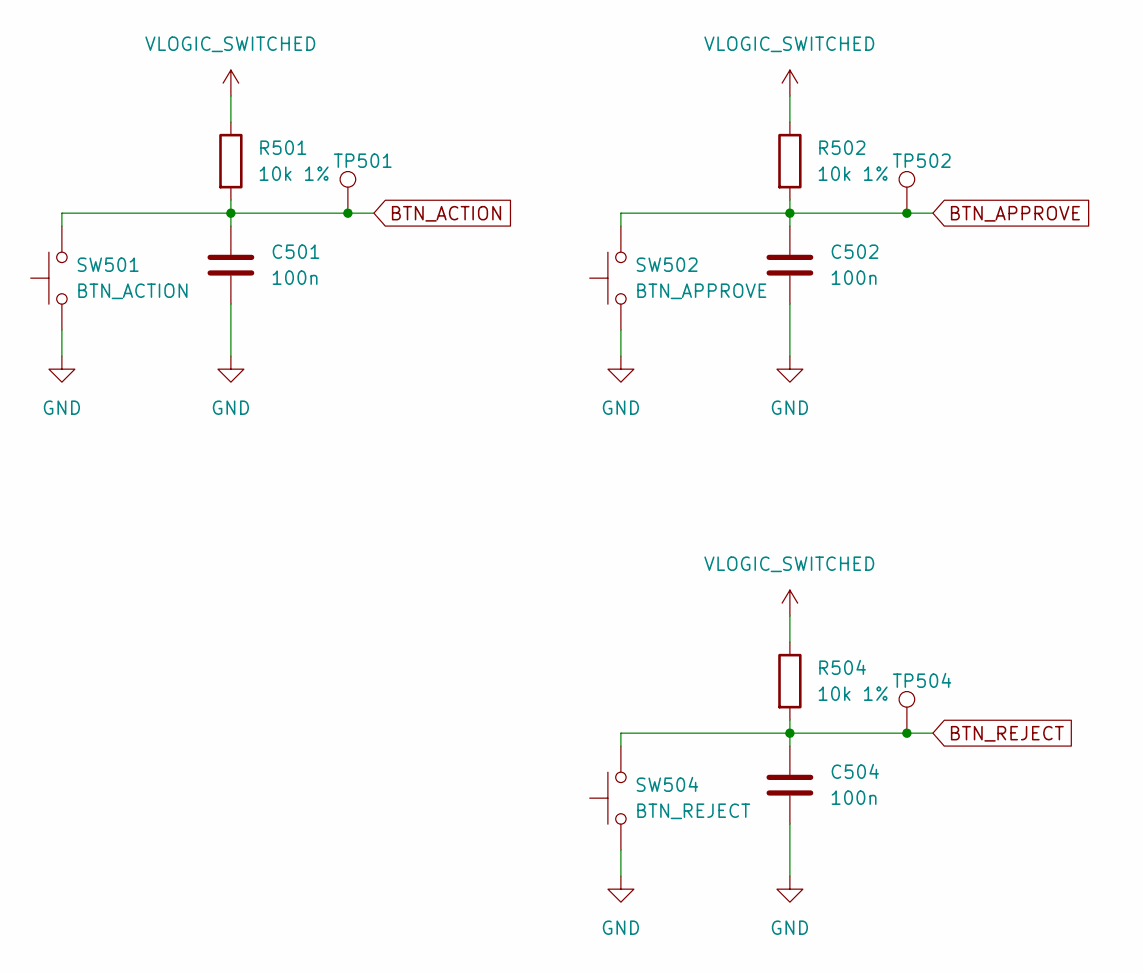
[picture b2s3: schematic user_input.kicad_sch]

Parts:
C501, C502, C504: 100n; C_0603_1608Metric_Pad1.08x0.95mm_HandSolder; LCSC Part C14663
R501, R502, R504: 10k 1%; R_0603_1608Metric_Pad0.98x0.95mm_HandSolder; LCSC Part C98220
SW501: BTN_ACTION; SW_Push_1P1T_XKB_TS-1187A; LCSC Part C318884
SW502: BTN_APPROVE; SW_Push_1P1T_XKB_TS-1187A; LCSC Part C318884
SW504: BTN_REJECT; SW_Push_1P1T_XKB_TS-1187A; LCSC Part C318884
TP501, TP502, TP504: TestPoint; TestPoint_Pad_D1.0mm

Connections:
BTN_ACTION: C501.1, R501.2, SW501.2, TP501.1 (1_1); also elsewhere on the board
BTN_APPROVE: C502.1, R502.2, SW502.2, TP502.1 (1_1); also elsewhere on the board
BTN_REJECT: C504.1, R504.2, SW504.2, TP504.1 (1_1); also elsewhere on the board
GND: C501.2, C502.2, C504.2, SW501.1, SW502.1, SW504.1; also elsewhere on the board
VLOGIC_SWITCHED: R501.1, R502.1, R504.1; also elsewhere on the board
